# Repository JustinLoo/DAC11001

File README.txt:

the ape4ad5791 is the finished design by GH, the DAC11001 is my design that im basing off of the ape4ad5791. the goal is to make ape4ad5791 but with a different main IC being the DAC11001. both layout connections should be the same. same io and interface.

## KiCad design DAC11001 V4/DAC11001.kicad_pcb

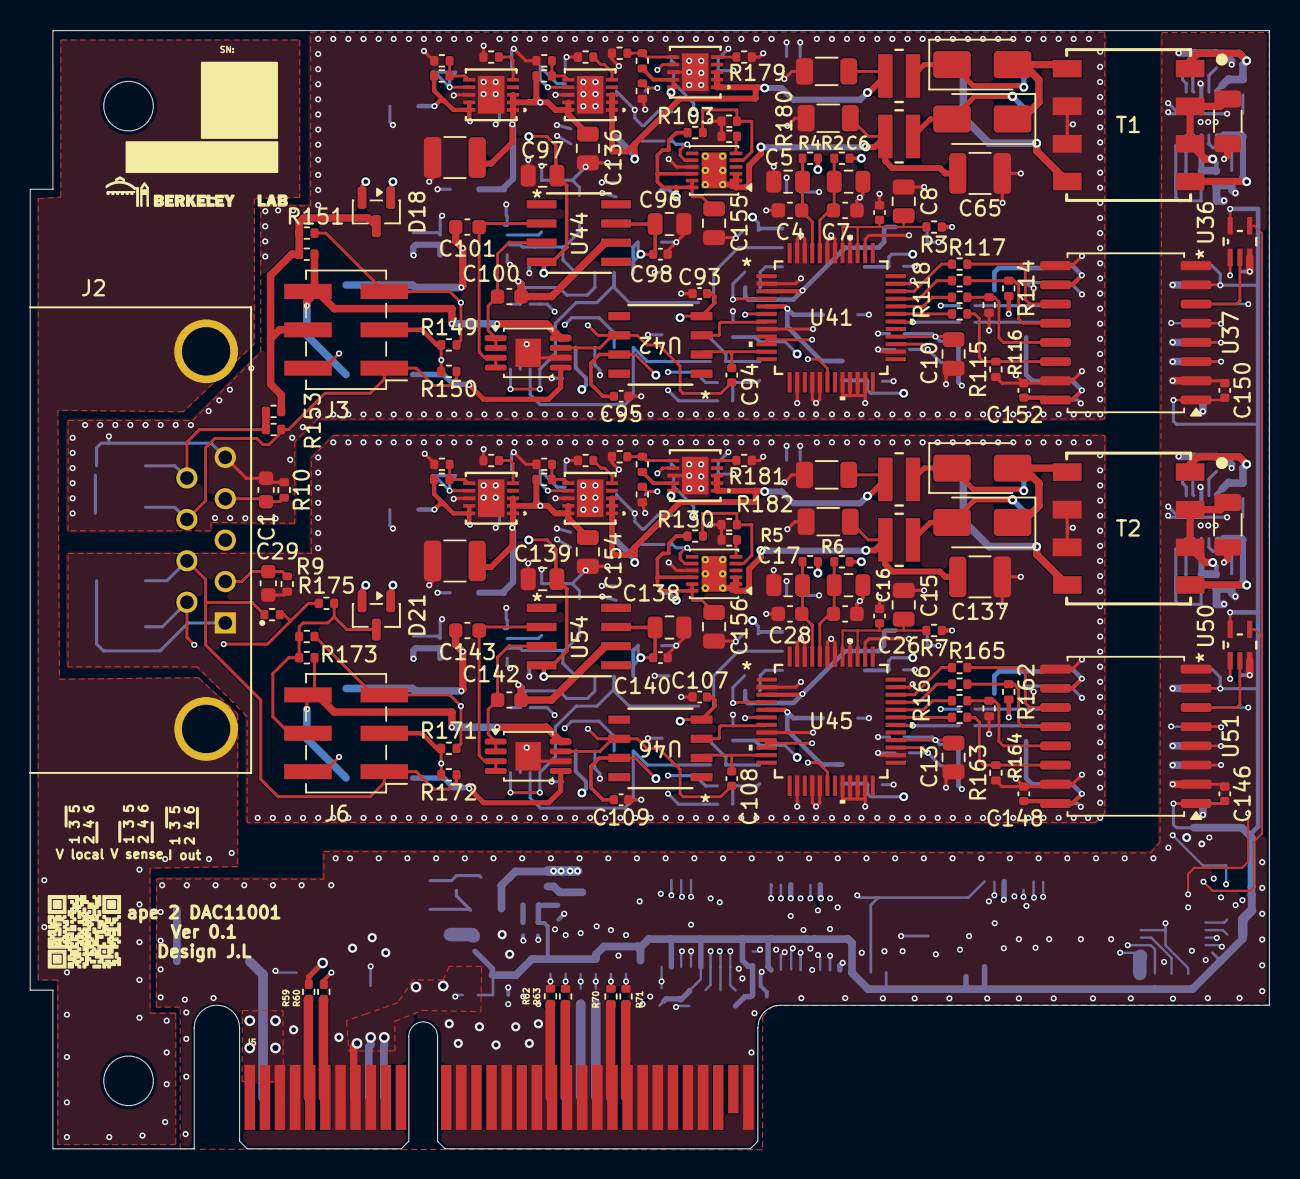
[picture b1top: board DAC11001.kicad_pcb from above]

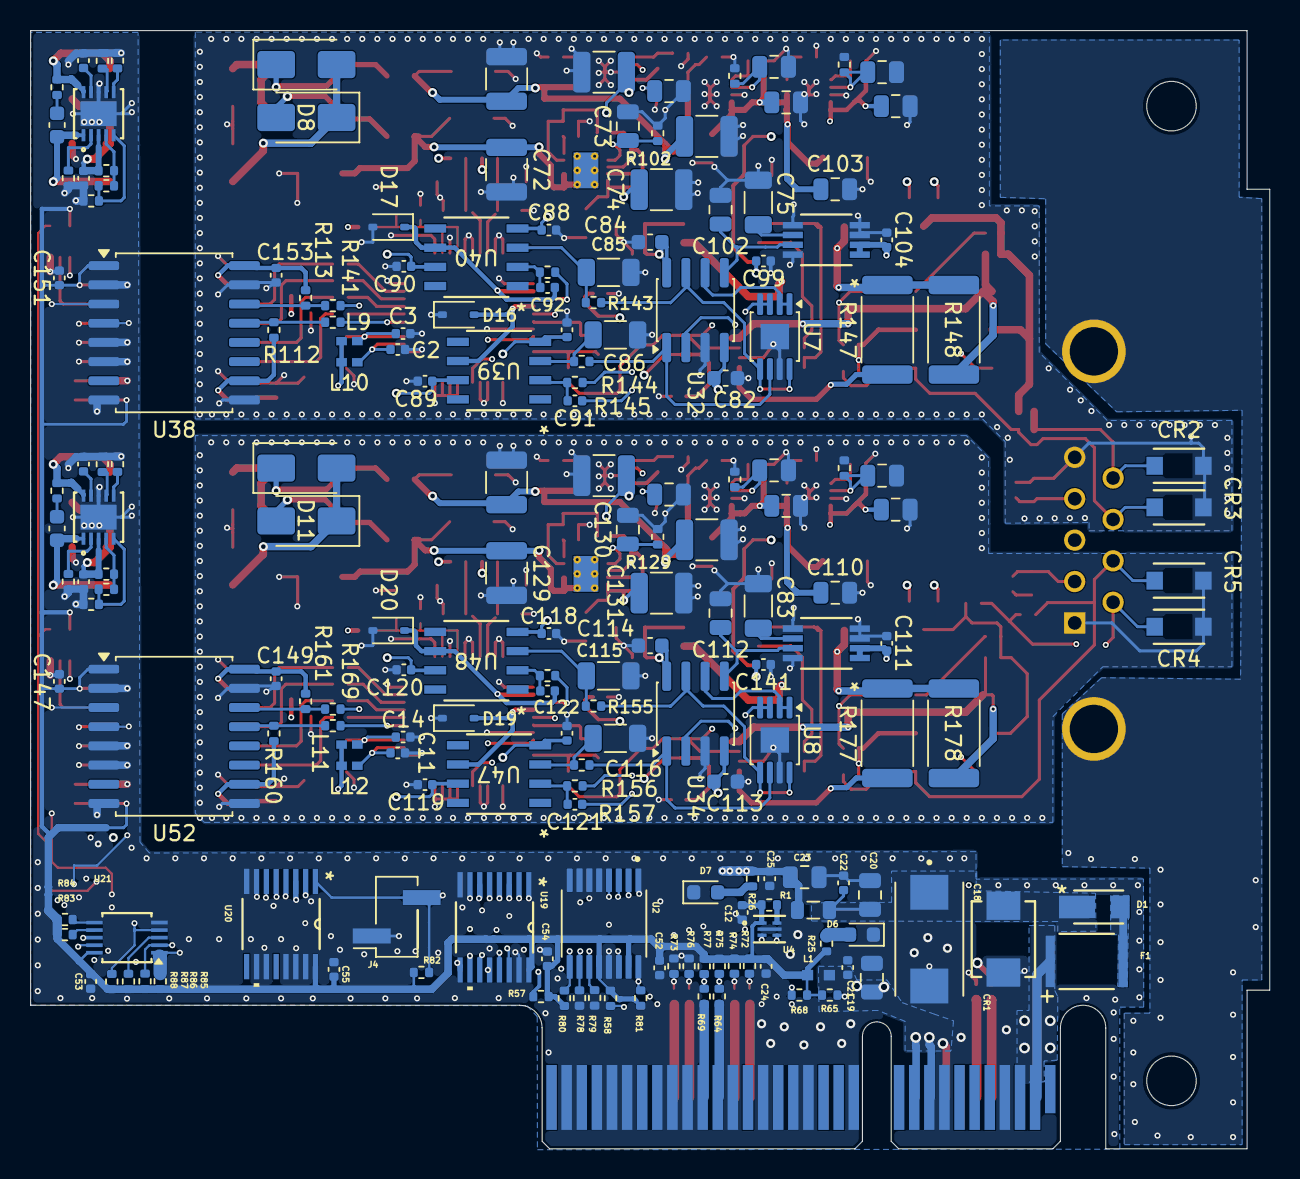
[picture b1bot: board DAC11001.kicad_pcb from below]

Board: 6 copper layers, 82.0 x 74.0 mm, 340 parts (188 on the bottom side), 200 nets.

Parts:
C1, C29: 1nF 50V C0G; C_0603_1608Metric
C2, C3, C11, C14, C87, C88, C89, C90, C93, C95, C107, C109, C117, C118, C119, C120, C146, C147, C148, C149, C150, C151, C152, C153: 0.1uF 50V X7R; C_0402_1005Metric
C4, C7, C26, C28: 1uF 50V X7R; C_0603_1608Metric
C5, C6, C16, C17, C96, C97, C103, C110, C138, C139: 10uF 35V X5R; C_0805_2012Metric
C8, C10, C13, C15, C19: 10uF 16V X5R; C_0805_2012Metric
C9, C27: 1uF 16V X5R; C_0402_1005Metric
C12, C21, C22, C24, C25, C52, C53, C54, C55, C98, C99, C104, C105, C111, C133, C140, C141: 100nF 50V X7R; C_0402_1005Metric
C18: 100uF 25V; CAPPM7343X310N
C20, C23, C67, C70, C73, C77, C80, C124, C127, C130: 4.7uF 50V X5R; C_0805_2012Metric
C62, C134: 180pF C0G 100V; C_0603_1608Metric
C63, C135: 0.01uF 50V X7R; C_0402_1005Metric
C65, C66, C68, C69, C71, C72, C123, C125, C126, C128, C129, C137: 10uF 50V X7R; C_1210_3225Metric
C74, C131: 22uF 35V X7R; C_1210_3225Metric
C75, C83, C85, C86, C115, C116: 1uF C0G 25V; C_1206_3216Metric
C76, C78, C79, C81, C102, C112, C136, C154, C155, C156: 10uF 25V X7R; C_0805_2012Metric
C82, C84, C113, C114: 0.1uF 50V X7R; C_0603_1608Metric
C91, C92, C94, C108, C121, C122: 100pF 50V C0G; C_0402_1005Metric
C100, C142: 10pF 50V C0G; C_0603_1608Metric
C101, C143: 22pF 50V C0G; C_0603_1608Metric
C106, C132: 10uF 25V X7R; C_1206_3216Metric
CR1: SMBJ15A; DO-214AASMB_J-BEND_LTF
CR2, CR3, CR4, CR5: SMF13CA; SOD-123F_LTF
D1: DFLS130-7; DFLS130-7_DIO
D4, D5, D8, D9, D10, D11, D12, D13: CMSH1-200HE; D_SMA
D6: LTST-C193KRKT-5A; LED_0603_1608Metric
D7: LTST-C193TBKT-5A; LED_0603_1608Metric
D16, D17, D19, D20: RB751V40; D_SOD-323
D18, D21: BAV199; SOT-23
F1: Polyfuse; FUS_MINISMDC110F_TYCO_TYC
J2: LD09S13A4GV00LF; AMPHENOL_LD09S13A4GV00LF
J3, J6: Conn_02x03_Odd_Even; PinHeader_2x03_P2.54mm_Vertical_SMD
J4: Conn_01x02; PinHeader_1x02_P2.54mm_Vertical_SMD_Pin1Right
J5: Bus_PCI_Express_x4; BUS_PCIexpress_x4_noedge
L1: WE-CBF_0603; WE-CBF_0603_W2.2
L2: BLM21PG221SN1D; L_0805_2012Metric
L5, L6, L7, L8: 39uH; IND_XFL3012_COC
L9, L10, L11, L12: BLM15AG601SN1D; IND_BLM15_0402_MUR
R1: 4k75; R_0402_1005Metric
R2, R3, R6, R7: 10; R_0402_1005Metric
R4, R5: 1; R_0402_1005Metric
R9, R10, R57, R58, R65, R68, R72, R73, R74, R75, R76, R77, R78, R79, R80, R81, R82, R83, R84, R85, R86, R87, R88, R96, R100, R108, R112, R113, R114, R115, R116, R119, R123, R127, R160, R161, R162, R163, R164: 10k; R_0402_1005Metric
R25: 1.2k; R_0402_1005Metric
R26: 18k; R_0402_1005Metric
R56, R132: 715k; R_0402_1005Metric
R59, R60, R143, R144, R154, R155, R156, R176: 100; R_0402_1005Metric
R61, R133: 36.5k; R_0402_1005Metric
R62, R63, R64, R69, R70, R71, R153, R175: 50; R_0402_1005Metric
R66, R134: 66.5k; R_0402_1005Metric
R67, R135: 49.9k; R_0402_1005Metric
R89, R136: 14.7k; R_0402_1005Metric
R90, R137: 12.1k; R_0402_1005Metric
R91, R138: 39k; R_0402_1005Metric
R93, R124: 1.24k; R_0402_1005Metric
R94, R125: 121k 0.1%; R_0402_1005Metric
R95, R126: 348k; R_0402_1005Metric
R97, R120: 750; R_0402_1005Metric
R98, R121: 154k 0.1%; R_0402_1005Metric
R99, R122: 442k; R_0402_1005Metric
R101, R128: 22.6k; R_0402_1005Metric
R102, R129: 165k 0.1%; R_0402_1005Metric
R103, R130: 220k; R_0402_1005Metric
R104, R131: 4.99k; R_0402_1005Metric
R105, R109: 2.49k; R_0402_1005Metric
R106, R110: 49.9k 0.1%; R_0402_1005Metric
R107, R111: 140k; R_0402_1005Metric
R117, R118, R139, R140, R141, R142, R165, R166, R167, R168, R169, R170: 33; R_0402_1005Metric
R145, R146, R157, R158: 22; R_0402_1005Metric
R147, R148, R177, R178: 500 0.01%; R_2512_6332Metric
R149, R150, R151, R152, R171, R172, R173, R174: 0; R_0402_1005Metric
R179, R180, R181, R182: 1.8k; R_1206_3216Metric
T1, T2: WE-PPTI_EP7; WE-PPTI_EP7_L9.14W9.78H10.54
U2: SC18IS606PWJ; SOP65P640X110-16N
U3, U6: LT3999EDD-PBF; WFDFN10_3X3_ADI
U4: M24128-BFMH6TG; UFDFPN5_1P7X1P4_STM
U7, U8: LT5400AIMS8E-1-PBF; MSOP-8-1EP_3x3mm_P0.65mm_EP1.68x1.88mm
U19, U20: SN74LVC157APWR; PW16
U21: PCA9537; TSSOP-10_3x3mm_P0.5mm
U23, U24, U27, U30, U31, U35: LT3042IDD-TRPBF; DFN-10_DD_LIT
U28, U49: LT3094xDD; DFN-12-1EP_3x3mm_P0.45mm_EP1.65x2.38mm_ThermalVias
U29, U33: LTC6655LNBHMS8-5-PBF; 05-08-1660_ADI
U32, U34: OPA2189xD; SOIC-8_3.9x4.9mm_P1.27mm
U36, U50: SN74LVC1G125DCKR; DCK5
U37, U51: ADuM1401xRW; SOIC-16W_7.5x10.3mm_P1.27mm
U38, U52: ADuM1400xRW; SOIC-16W_7.5x10.3mm_P1.27mm
U39, U40, U42, U46, U47, U48: OPA828ID; D8_TEX
U41, U45: DAC11001BPFBT; PQFP48_DAC11001_TEX
U43, U53: LT5400ACMS8E-1-PBF-func; MSOP-8-1EP_3x3mm_P0.65mm_EP1.68x1.88mm
U44, U54: ADA4523-1BRZ; R-8_ADI

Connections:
/DC3V3: C19.1, C21.1, J5.A9 (+3.3V), J5.A10 (+3.3V), J5.B8 (+3.3V), L1.1
/DC12V: F1.1, J5.A2 (+12V), J5.A3 (+12V), J5.B1 (+12V), J5.B2 (+12V), J5.B3 (+12V)
/HSI1N: J5.A22 (PERn1), R69.1
/HSI1P: J5.A21 (PERp1), R64.1
/HSO1N: J5.B20 (PETn1), R63.1
/HSO1P: J5.B19 (PETp1), R62.1
/HSO2N: J5.B24 (PETn2), R71.1
/HSO2P: J5.B23 (PETp2), R70.1
/I2C_SCL: R59.1, R65.2, U2.2 (SCL), U4.4 (SCL), U21.8 (SCL)
/I2C_SDA: R60.1, R68.2, U2.1 (SDA), U4.3 (SDA), U21.9 (SDA)
/OUT1: CR2.1, J2.09, R153.1, R154.2
/OUT2: CR4.1, J2.06, R175.1, R176.2
/SENSE1: CR3.1, J2.08, J3.1, R150.1, R154.1
/SENSE2: CR5.1, J2.07, J6.1, R172.1, R176.1
/SGND1: C1.2, J2.04, R10.2
/SGND2: C29.2, J2.02, R9.2
/SHIELD: J2.SH1 (SHIELD), J2.SH2 (SHIELD)
/ctrlpins/A0B1: J4.2, R82.2, U19.1 (A/*B), U20.1 (A/*B)
/ctrlpins/VDD: C12.1, C24.1, C52.1, C53.1, C54.1, C55.1, C146.1, C147.1, C150.1, C151.1, L1.2, R1.1, R25.1, R57.1, R58.1, R65.1, R68.1, R72.1, R74.1, R75.1, R77.2, R80.2, R81.2, R82.1, R83.2, R84.2, R85.2, R86.2, R87.2, R88.2, U2.12 (VDD), U2.15 (VREFP), U4.1 (VCC), U19.16 (VCC), U20.16 (VCC), U21.10 (VDD), U36.5 (VCC), U37.1 (VDD1), U37.7 (VE1), U38.1 (VDD1), U50.5 (VCC), U51.1 (VDD1), U51.7 (VE1), U52.1 (VDD1)
/ctrlpins/exCSB1: R62.2, R72.2, U19.11 (3A)
/ctrlpins/exCSB2: R63.2, R74.2, U19.14 (4A)
/ctrlpins/exLDAC: R64.2, R75.2, U20.2 (1A), U20.5 (2A)
/ctrlpins/exMISO: R69.2, R77.1, U2.14 (MISO), U36.4 (Y), U50.4 (Y)
/ctrlpins/exMOSI: R70.2, R76.1, U19.5 (2A)
/ctrlpins/exSCLK: R71.2, R73.1, U19.2 (1A)
/ctrlpins/i2cCSB1: R80.1, U2.9 (~SS0/GPIO0), U19.10 (3B)
/ctrlpins/i2cCSB2: R81.1, U2.16 (~SS1/GPIO1), U19.13 (4B)
/ctrlpins/i2cLDAC1: R85.1, U20.3 (1B), U21.1 (IO0)
/ctrlpins/i2cLDAC2: R86.1, U20.6 (2B), U21.2 (IO1)
/ctrlpins/i2cMOSI1: R78.2, U2.10 (MOSI), U19.6 (2B)
/ctrlpins/i2cSCLK1: R79.2, U2.11 (SPICLK), U19.3 (1B)
/eeprom/WC: R1.2, U4.5 (WC)
/pcie4x/I2CCLK: J5.B5 (SMCLK), R59.2
/pcie4x/I2CSDA: J5.B6 (SMDAT), R60.2
/powerin/DC12Vout: C23.1, C25.1, C105.1, C106.1, C132.1, C133.1, L2.2, R26.1, R56.1, R132.1, T1.2, T1.3, T2.2, T2.3, U3.3 (VIN), U6.3 (VIN)
/top_1/DAC11001/DVDD: C78.1, C152.1, C153.1, L9.1, L10.1, R3.1, R107.1, R112.2, R113.2, R114.2, U30.9 (OUTS), U30.10 (OUT), U37.10 (VE2), U37.16 (VDD2), U38.10 (VE2), U38.16 (VDD2)
/top_1/DAC11001/RCM: C94.1, U41.11 (RCM), U42.2 ('-IN)
/top_1/DAC11001/RFB: J3.3, R149.1, R150.2, U41.9 (RFB), U41.10 (ROFS)
/top_1/DAC11001/V_DAC_OUT: U41.7 (OUT), U42.3 ('+IN)
/top_1/DAC11001/V_REFNF: C91.1, D16.2 (A), U39.6 (OUT), U41.5 (REFNF)
/top_1/DAC11001/V_REFNS: R145.2, U41.6 (REFNS)
/top_1/DAC11001/V_REFPF: C92.1, D17.1 (K), U40.6 (OUT), U41.3 (REFPF)
/top_1/DAC11001/V_REFPS: R146.2, U41.4 (REFPS)
/top_1/I_CLR: R140.2, U41.30 (CLR)
/top_1/I_LDAC: R141.2, U41.18 (LDAC)
/top_1/I_SCLK: R142.2, U41.31 (SCLK)
/top_1/I_SDIN: R139.2, U41.32 (SDIN)
/top_1/I_SDO: R117.2, U41.34 (SDO)
/top_1/I_SYNC: R118.2, U41.33 (SYNC)
/top_1/LT3042/V_P_+18.5V: C66.1, C69.1, L5.1, R179.1, U23.1 (IN), U23.2 (IN), U23.3 (EN/UV), U27.1 (IN), U27.2 (IN), U27.3 (EN/UV)
/top_1/LT3042v2/V_P_+12V: C68.1, C76.1, C103.1, C104.1, C136.1, R95.1, U23.9 (OUTS), U23.10 (OUT), U29.1 (*SHDN), U29.2 (VIN), U30.1 (IN), U30.2 (IN), U30.3 (EN/UV)
/top_1/LT3094/V_P_-18.5V: C65.1, C72.1, L6.1, R180.1, U28.1 (IN), U28.2 (IN), U28.3 (EN/UV), U28.13 (IN)
/top_1/LTC6655/V_LN_5: C102.1, U29.7 (VOUT_F), U32.5 (+)
/top_1/OPA2189/r1in: U7.1 (R1), U7.2 (R2), U32.6 (-)
/top_1/OPA2189/r1out: R143.2, U7.5 (R4), U7.8 (R1), U32.7
/top_1/OPA2189/r3in: U7.3 (R3), U7.4 (R4), U32.2 (-)
/top_1/OPA2189/r3out: R144.2, U7.6 (R3), U32.1
/top_1/OUT STAGE/howland/Iout: J3.6, R148.1, R152.1, U43.8 (R1)
/top_1/OUT STAGE/howland/Vin: C94.2, J3.2, J3.5, R149.2, R151.2, U42.6 (OUT), U43.7 (R2)
/top_1/V_P_C_+15.4V: C71.1, C84.1, C89.1, C90.1, C95.1, C96.1, C98.1, D18.2, R4.1, R99.1, U27.9 (OUTS), U27.10 (OUT), U32.8 (V+), U39.7 (V+), U40.7 (V+), U42.7 (V+), U44.7 (V+)
/top_1/V_P_C_-16.5V: C74.1, C82.1, C87.1, C88.1, C93.1, C97.2, C99.2, C155.1, D18.1, R2.1, R103.1, U28.10 (OUTS), U28.11 (OUT), U28.12 (OUT), U32.4 (V-), U39.4 (V-), U40.4 (V-), U42.4 (V-), U44.4 (V-)
/top_1/adum/VIA1: U19.4 (1Y), U37.3 (VIA), U51.3 (VIA)
/top_1/adum/VIA2: U20.4 (1Y), U38.3 (VIA)
/top_1/adum/VIB1: U19.7 (2Y), U37.4 (VIB), U51.4 (VIB)
/top_1/adum/VIB2: R88.1, U21.4 (IO3), U38.4 (VIB), U52.4 (VIB)
/top_1/adum/VIC1: U19.9 (3Y), U36.1 (*OE), U37.5 (VIC)
/top_1/adum/VID1: R117.1, U37.11 (VID)
/top_1/adum/VOA1: R115.2, R142.1, U37.14 (VOA)
/top_1/adum/VOA2: R113.1, R141.1, U38.14 (VOA)
/top_1/adum/VOB1: R116.2, R139.1, U37.13 (VOB)
/top_1/adum/VOB2: R112.1, R140.1, U38.13 (VOB)
/top_1/adum/VOC1: R114.1, R118.1, U37.12 (VOC)
/top_1/adum/VOD1: U36.2 (A), U37.6 (VOD)
/top_2/DAC11001/DVDD: C81.1, C148.1, C149.1, L11.1, L12.1, R7.1, R111.1, R160.2, R161.2, R162.2, U31.9 (OUTS), U31.10 (OUT), U51.10 (VE2), U51.16 (VDD2), U52.10 (VE2), U52.16 (VDD2)
/top_2/DAC11001/RCM: C108.1, U45.11 (RCM), U46.2 ('-IN)
/top_2/DAC11001/RFB: J6.3, R171.1, R172.2, U45.9 (RFB), U45.10 (ROFS)
/top_2/DAC11001/V_DAC_OUT: U45.7 (OUT), U46.3 ('+IN)
/top_2/DAC11001/V_REFNF: C121.1, D19.2 (A), U45.5 (REFNF), U47.6 (OUT)
/top_2/DAC11001/V_REFNS: R157.2, U45.6 (REFNS)
/top_2/DAC11001/V_REFPF: C122.1, D20.1 (K), U45.3 (REFPF), U48.6 (OUT)
/top_2/DAC11001/V_REFPS: R158.2, U45.4 (REFPS)
/top_2/I_CLR: R168.2, U45.30 (CLR)
/top_2/I_LDAC: R169.2, U45.18 (LDAC)
/top_2/I_SCLK: R170.2, U45.31 (SCLK)
/top_2/I_SDIN: R167.2, U45.32 (SDIN)
/top_2/I_SDO: R165.2, U45.34 (SDO)
/top_2/I_SYNC: R166.2, U45.33 (SYNC)
/top_2/LT3042/V_P_+18.5V: C123.1, C126.1, L7.1, R181.1, U24.1 (IN), U24.2 (IN), U24.3 (EN/UV), U35.1 (IN), U35.2 (IN), U35.3 (EN/UV)
/top_2/LT3042v2/V_P_+12V: C79.1, C110.1, C111.1, C128.1, C154.1, R126.1, U24.9 (OUTS), U24.10 (OUT), U31.1 (IN), U31.2 (IN), U31.3 (EN/UV), U33.1 (*SHDN), U33.2 (VIN)
/top_2/LT3094/V_P_-18.5V: C129.1, C137.1, L8.1, R182.1, U49.1 (IN), U49.2 (IN), U49.3 (EN/UV), U49.13 (IN)
/top_2/LTC6655/V_LN_5: C112.1, U33.7 (VOUT_F), U34.5 (+)
/top_2/OPA2189/r1in: U8.1 (R1), U8.2 (R2), U34.6 (-)
/top_2/OPA2189/r1out: R155.2, U8.5 (R4), U8.8 (R1), U34.7
/top_2/OPA2189/r3in: U8.3 (R3), U8.4 (R4), U34.2 (-)
/top_2/OPA2189/r3out: R156.2, U8.6 (R3), U34.1
/top_2/OUT STAGE/howland/Iout: J6.6, R174.1, R178.1, U53.8 (R1)
/top_2/OUT STAGE/howland/Vin: C108.2, J6.2, J6.5, R171.2, R173.2, U46.6 (OUT), U53.7 (R2)
/top_2/V_P_C_+15.4V: C109.1, C114.1, C119.1, C120.1, C125.1, C138.1, C140.1, D21.2, R5.1, R122.1, U34.8 (V+), U35.9 (OUTS), U35.10 (OUT), U46.7 (V+), U47.7 (V+), U48.7 (V+), U54.7 (V+)
/top_2/V_P_C_-16.5V: C107.1, C113.1, C117.1, C118.1, C131.1, C139.2, C141.2, C156.1, D21.1, R6.1, R130.1, U34.4 (V-), U46.4 (V-), U47.4 (V-), U48.4 (V-), U49.10 (OUTS), U49.11 (OUT), U49.12 (OUT), U54.4 (V-)
/top_2/adum/VIA2: U20.7 (2Y), U52.3 (VIA)
/top_2/adum/VIC1: U19.12 (4Y), U50.1 (*OE), U51.5 (VIC)
/top_2/adum/VID1: R165.1, U51.11 (VID)
/top_2/adum/VOA1: R163.2, R170.1, U51.14 (VOA)
/top_2/adum/VOA2: R161.1, R169.1, U52.14 (VOA)
/top_2/adum/VOB1: R164.2, R167.1, U51.13 (VOB)
/top_2/adum/VOB2: R160.1, R168.1, U52.13 (VOB)
/top_2/adum/VOC1: R162.1, R166.1, U51.12 (VOC)
/top_2/adum/VOD1: U50.2 (A), U51.6 (VOD)
GND: C12.2, C18.2, C19.2, C20.2, C21.2, C22.2, C23.2, C24.2, C25.2, C52.2, C53.2, C54.2, C55.2, C63.2, C105.2, C106.2, C132.2, C133.2, C135.2, C146.2, C147.2, C150.2, C151.2, CR1.2, D6.1 (K), D7.1 (K), J4.1, J5.A4 (GND), J5.A8 (JTAG5), J5.A12 (GND), J5.A15 (GND), J5.A18 (GND), J5.A20 (GND), J5.A23 (GND), J5.A24 (GND), J5.A27 (GND), J5.A28 (GND), J5.A31 (GND), J5.B4 (GND), J5.B7 (GND), J5.B9 (JTAG1), J5.B13 (GND), J5.B16 (GND), J5.B18 (GND), J5.B21 (GND), J5.B22 (GND), J5.B25 (GND), J5.B26 (GND), J5.B29 (GND), J5.B32 (GND), R66.2, R67.2, R73.2, R76.2, R78.1, R79.1, R89.2, R90.2, R134.2, R135.2, R136.2, R137.2, U2.5 (A2), U2.6 (A1), U2.7 (A0), U2.13 (VSS), U3.8 (SYNC), U3.11 (GND), U4.2 (VSS), U6.8 (SYNC), U6.11 (GND), U19.8 (GND), U19.15 (*G), U20.8 (GND), U20.10 (3B), U20.11 (3A), U20.13 (4B), U20.14 (4A), U20.15 (*G), U21.5 (VSS), U36.3 (GND), U37.2 (GND1), U37.8 (GND1), U38.2 (GND1), U38.5 (VIC), U38.6 (VID), U38.8 (GND1), U50.3 (GND), U51.2 (GND1), U51.8 (GND1), U52.2 (GND1), U52.5 (VIC), U52.6 (VID), U52.8 (GND1)
GNDA1: C1.1, C2.2, C3.2, C4.2, C5.2, C6.2, C7.2, C8.2, C9.2, C10.2, C65.2, C66.2, C67.2, C68.2, C69.2, C70.2, C71.2, C72.2, C73.2, C74.2, C75.2, C76.2, C77.2, C78.2, C82.2, C84.2, C85.2, C86.2, C87.2, C88.2, C89.2, C90.2, C93.2, C95.2, C96.2, C97.1, C98.2, C99.1, C102.2, C103.2, C104.2, C136.2, C152.2, C153.2, C155.2, CR2.2, CR3.2, D16.1 (K), D17.2 (A), J2.05, R10.1, R93.2, R94.2, R96.2, R97.2, R98.2, R100.2, R101.2, R102.2, R104.2, R105.2, R106.2, R108.2, R115.1, R116.1, R179.2, R180.2, T1.6, T1.7, U7.7 (R2), U7.9 (EP), U23.8 (GND), U23.11 (GND), U27.8 (GND), U27.11 (GND), U28.9 (GND), U29.3 (GND), U29.4 (GND), U29.5 (GND), U29.8 (GND), U30.8 (GND), U30.11 (GND), U32.3 (+), U37.9 (GND2), U37.15 (GND2), U38.9 (GND2), U38.15 (GND2), U41.2 (AGND), U41.8 (AGND-OUT), U41.14 (AGND-TNH), U41.16 (DGND), U41.17 (DGND), U41.20 (DGND), U41.21 (DGND), U41.22 (DGND), U41.23 (DGND), U41.26 (DGND), U41.35 (AGND), U41.38 (AGND), U41.40 (AGND), U41.42 (AGND), U41.43 (AGND), U41.46 (AGND), U41.47 (AGND), U43.6 (R3), U43.9 (EPAD)
GNDA2: C11.2, C13.2, C14.2, C15.2, C16.2, C17.2, C26.2, C27.2, C28.2, C29.1, C79.2, C80.2, C81.2, C83.2, C107.2, C109.2, C110.2, C111.2, C112.2, C113.2, C114.2, C115.2, C116.2, C117.2, C118.2, C119.2, C120.2, C123.2, C124.2, C125.2, C126.2, C127.2, C128.2, C129.2, C130.2, C131.2, C137.2, C138.2, C139.1, C140.2, C141.1, C148.2, C149.2, C154.2, C156.2, CR4.2, CR5.2, D19.1 (K), D20.2 (A), J2.01, R9.1, R109.2, R110.2, R119.2, R120.2, R121.2, R123.2, R124.2, R125.2, R127.2, R128.2, R129.2, R131.2, R163.1, R164.1, R181.2, R182.2, T2.6, T2.7, U8.7 (R2), U8.9 (EP), U24.8 (GND), U24.11 (GND), U31.8 (GND), U31.11 (GND), U33.3 (GND), U33.4 (GND), U33.5 (GND), U33.8 (GND), U34.3 (+), U35.8 (GND), U35.11 (GND), U45.2 (AGND), U45.8 (AGND-OUT), U45.14 (AGND-TNH), U45.16 (DGND), U45.17 (DGND), U45.20 (DGND), U45.21 (DGND), U45.22 (DGND), U45.23 (DGND), U45.26 (DGND), U45.35 (AGND), U45.38 (AGND), U45.40 (AGND), U45.42 (AGND), U45.43 (AGND), U45.46 (AGND), U45.47 (AGND), U49.9 (GND), U51.9 (GND2), U51.15 (GND2), U52.9 (GND2), U52.15 (GND2), U53.6 (R3), U53.9 (EPAD)
unnamed: C8.1, C9.1, R3.2, U41.39 (AVDD), U41.41 (AVDD)
unnamed: C15.1, C27.1, R7.2, U45.39 (AVDD), U45.41 (AVDD)
unnamed: C18.1, C20.1, C22.1, CR1.1, D1.C, L2.1
unnamed: C62.2, R91.1
unnamed: C134.2, R138.1
unnamed: D1.A, F1.2
unnamed: D4.2 (A), D8.1 (K), T1.5
unnamed: D4.1 (K), D9.1 (K), L5.2
unnamed: D6.2 (A), R25.2
unnamed: D7.2 (A), R26.2
unnamed: D8.2 (A), D10.2 (A), L6.2
unnamed: D9.2 (A), D10.1 (K), T1.8
unnamed: D11.2 (A), D13.2 (A), L8.2
unnamed: D5.2 (A), D11.1 (K), T2.5
unnamed: D12.2 (A), D13.1 (K), T2.8
unnamed: D5.1 (K), D12.1 (K), L7.2
unnamed: D18.3, J3.4, R151.1, R152.2, R153.2
unnamed: D21.3, J6.4, R173.1, R174.2, R175.2
unnamed: R147.1, U43.5 (R4)
unnamed: R177.1, U53.5 (R4)
unnamed: R58.2, U2.3 (~INT)
unnamed: R57.2, U2.4 (~RESET)
unnamed: C63.1, U3.9 (ILIM/SS)
unnamed: R61.2, R66.1, U3.5 (OVLO/DC)
unnamed: R67.1, U3.2 (RBIAS)
unnamed: R89.1, U3.6 (RDC)
unnamed: R90.1, U3.7 (RT)
unnamed: C62.1, T1.4, U3.1 (SWA)
unnamed: R91.2, T1.1, U3.10 (SWB)
unnamed: R56.2, R61.1, U3.4 (UVLO)
unnamed: C135.1, U6.9 (ILIM/SS)
unnamed: R133.2, R134.1, U6.5 (OVLO/DC)
unnamed: R135.1, U6.2 (RBIAS)
unnamed: R136.1, U6.6 (RDC)
unnamed: R137.1, U6.7 (RT)
unnamed: C134.1, T2.4, U6.1 (SWA)
unnamed: R138.2, T2.1, U6.10 (SWB)
unnamed: R132.2, R133.1, U6.4 (UVLO)
unnamed: R87.1, U21.3 (IO2)
unnamed: R83.1, U21.7 (~INT)
unnamed: R84.1, U21.6 (~RESET)
unnamed: R93.1, U23.5 (ILIM)
unnamed: R95.2, R96.1, U23.6 (PGFB)
unnamed: C67.1, R94.1, U23.7 (SET)
unnamed: R124.1, U24.5 (ILIM)
unnamed: R126.2, R127.1, U24.6 (PGFB)
unnamed: C127.1, R125.1, U24.7 (SET)
unnamed: R97.1, U27.5 (ILIM)
unnamed: R99.2, R100.1, U27.6 (PGFB)
unnamed: C70.1, R98.1, U27.7 (SET)
unnamed: R101.1, U28.6 (ILIM)
unnamed: R103.2, R104.1, U28.5 (PGFB)
unnamed: C73.1, R102.1, U28.8 (SET)
unnamed: C75.1, U29.6 (NR)
unnamed: R105.1, U30.5 (ILIM)
unnamed: R107.2, R108.1, U30.6 (PGFB)
unnamed: C77.1, R106.1, U30.7 (SET)
unnamed: R109.1, U31.5 (ILIM)
unnamed: R111.2, R119.1, U31.6 (PGFB)
unnamed: C80.1, R110.1, U31.7 (SET)
unnamed: C83.1, U33.6 (NR)
unnamed: R120.1, U35.5 (ILIM)
unnamed: R122.2, R123.1, U35.6 (PGFB)
unnamed: C124.1, R121.1, U35.7 (SET)
unnamed: C86.1, R144.1, U39.3 ('+IN)
unnamed: C91.2, R145.1, U39.2 ('-IN)
unnamed: C85.1, R143.1, U40.3 ('+IN)
unnamed: C92.2, R146.1, U40.2 ('-IN)
unnamed: C2.1, L10.2, U41.27 (DVDD)
unnamed: C3.1, C10.1, L9.2, U41.28 (IOVDD)
unnamed: C4.1, C5.1, R4.2, U41.45 (VCC)
unnamed: C6.1, C7.1, R2.2, U41.44 (VSS)
unnamed: C100.1, U43.1 (R1), U43.2 (R2), U44.3 (+IN)
unnamed: C101.1, U43.3 (R3), U43.4 (R4), U44.2 (-IN)
unnamed: C100.2, C101.2, R147.2, R148.2, U44.6 (OUT)
unnamed: C11.1, L12.2, U45.27 (DVDD)
unnamed: C13.1, C14.1, L11.2, U45.28 (IOVDD)
unnamed: C17.1, C28.1, R5.2, U45.45 (VCC)
unnamed: C16.1, C26.1, R6.2, U45.44 (VSS)
unnamed: C116.1, R156.1, U47.3 ('+IN)
unnamed: C121.2, R157.1, U47.2 ('-IN)
unnamed: C115.1, R155.1, U48.3 ('+IN)
unnamed: C122.2, R158.1, U48.2 ('-IN)
unnamed: R128.1, U49.6 (ILIM)
unnamed: R130.2, R131.1, U49.5 (PGFB)
unnamed: C130.1, R129.1, U49.8 (SET)
unnamed: C142.1, U53.1 (R1), U53.2 (R2), U54.3 (+IN)
unnamed: C143.1, U53.3 (R3), U53.4 (R4), U54.2 (-IN)
unnamed: C142.2, C143.2, R177.2, R178.2, U54.6 (OUT)

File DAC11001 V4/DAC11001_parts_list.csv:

Qty,References,Value,Footprint,Vendor,MPN,Manufacturer,DNP
2,C1 C29,1nF 50V C0G,C_0603_1608Metric,digikey:490-8275-1-ND,,,
24,C2 C3 C11 C14 C87 C88 C89 C90 C93 C95 C107 C109 C117 C118 C119 C120 C146 C147 C148 C149 C150 C151 C152 C153,0.1uF 50V X7R,C_0402_1005Metric,digikey:490-10700-1-ND,,,
4,C4 C7 C26 C28,1uF 50V X7R,C_0603_1608Metric,,,,
10,C5 C6 C16 C17 C96 C97 C103 C110 C138 C139,10uF 35V X5R,C_0805_2012Metric,digikey:490-12646-1-ND,,,
5,C8 C10 C13 C15 C19,10uF 16V X5R,C_0805_2012Metric,digikey:490-18663-1-ND,,,
2,C9 C27,1uF 16V X5R,C_0402_1005Metric,digikey:490-10018-1-ND,,,
17,C12 C21 C22 C24 C25 C52 C53 C54 C55 C98 C99 C104 C105 C111 C133 C140 C141,100nF 50V X7R,C_0402_1005Metric,digikey:490-10700-1-ND,,,
1,C18,100uF 25V,CAPPM7343X310N,digikey:718-2173-1-ND,,,
10,C20 C23 C67 C70 C73 C77 C80 C124 C127 C130,4.7uF 50V X5R,C_0805_2012Metric,digikey:490-10751-1-ND,,,
2,C62 C134,180pF C0G 100V,C_0603_1608Metric,,GRM3195C2A181JA01D,Murata,
2,C63 C135,0.01uF 50V X7R,C_0402_1005Metric,,,,
12,C65 C66 C68 C69 C71 C72 C123 C125 C126 C128 C129 C137,10uF 50V X7R,C_1210_3225Metric,,GRM32ER71H106KA12L,Murata,
2,C74 C131,22uF 35V X7R,C_1210_3225Metric,,GRM32ER7YA226MA12L,Murata,
6,C75 C83 C85 C86 C115 C116,1uF C0G 25V,C_1206_3216Metric,,C3216C0G1E105J160AC,TDK,
10,C76 C79 C136 C154 C155 C156 C78 C81 C102 C112,10uF 25V X7R,C_0805_2012Metric,,"C2012X7R1E106K125AB, CL31B106KAHNNNE, GRM21BR71E106KA73L",TDK,
4,C82 C84 C113 C114,0.1uF 50V X7R,C_0603_1608Metric,,,,
6,C91 C92 C94 C108 C121 C122,100pF 50V C0G,C_0402_1005Metric,,,,
2,C100 C142,10pF 50V C0G,C_0603_1608Metric,digikey:490-6086-1-ND,,,
2,C101 C143,22pF 50V C0G,C_0603_1608Metric,digikey:490-16699-1-ND,,,
2,C106 C132,10uF 25V X7R,C_1206_3216Metric,,GRM32ER71H106KA12L,Murata,
1,CR1,SMBJ15A,DO-214AASMB_J-BEND_LTF,digikey:SMBJ15ALFCT-ND,,,
4,CR2 CR3 CR4 CR5,SMF13CA,SOD-123F_LTF,digikey:SMF13CA,,,
1,D1,DFLS130-7,DFLS130-7_DIO,digikey:DFLS130DICT-ND,,,
8,D4 D5 D8 D9 D10 D11 D12 D13,CMSH1-200HE,D_SMA,,,,
1,D6,LTST-C193KRKT-5A,LED_0603_1608Metric,digikey:160-1830-1-ND,,,
1,D7,LTST-C193TBKT-5A,LED_0603_1608Metric,digikey:160-1827-1-ND,,,
4,D16 D17 D19 D20,RB751V40,D_SOD-323,,RB751V40T1G,onsemi,
2,D18 D21,BAV199,SOT-23,digikey:5399-BAV199CT-ND,,,
1,F1,Polyfuse,FUS_MINISMDC110F_TYCO_TYC,digikey:MINISMDC110F-2CT-ND,,,
1,J2,LD09S13A4GV00LF,AMPHENOL_LD09S13A4GV00LF,digikey:609-5188-ND,,,
2,J3 J6,Conn_02x03_Odd_Even,PinHeader_2x03_P2.54mm_Vertical_SMD,digikey:WM17457-ND,,,
1,J4,Conn_01x02,PinHeader_1x02_P2.54mm_Vertical_SMD_Pin1Right,digikey:SAM8979-ND,,,
1,J5,Bus_PCI_Express_x4,BUS_PCIexpress_x4_noedge,,,,
1,L1,WE-CBF_0603,WE-CBF_0603_W2.2,digikey:732-1582-1-ND,,,
1,L2,BLM21PG221SN1D,L_0805_2012Metric,digikey:490-1054-1-ND,BLM21PG221SN1D,Murata,
4,L5 L6 L7 L8,39uH,IND_XFL3012_COC,,XFL3012-393MEC,Coilcraft,
4,L9 L10 L11 L12,BLM15AG601SN1D,IND_BLM15_0402_MUR,,BLM15AG601SN1D,Murata,
1,R1,4k75,R_0402_1005Metric,digikey:YAG1271CT-ND,,,DNP
4,R2 R3 R6 R7,10,R_0402_1005Metric,digikey:YAG3438CT-ND,,,
2,R4 R5,1,R_0402_1005Metric,,,,
37,R9 R10 R57 R58 R72 R73 R74 R75 R76 R77 R78 R79 R80 R81 R82 R83 R84 R85 R86 R87 R88 R96 R100 R108 R112 R113 R114 R115 R116 R119 R123 R127 R160 R161 R162 R163 R164,10k,R_0402_1005Metric,digikey:311-10KJRCT-ND,,,
1,R25,1.2k,R_0402_1005Metric,digikey:311-1.2KJRCT-ND,,,
1,R26,18k,R_0402_1005Metric,digikey:311-18.0KLRCT-ND,,,
2,R56 R132,715k,R_0402_1005Metric,,,,
8,R59 R60 R143 R144 R154 R155 R156 R176,100,R_0402_1005Metric,digikey:YAG3435CT-ND,,,
2,R61 R133,36.5k,R_0402_1005Metric,,,,
8,R62 R63 R64 R69 R70 R71 R153 R175,50,R_0402_1005Metric,digikey:13-RT0402BRE0750RLCT-ND,,,
2,R65 R68,10k,R_0402_1005Metric,digikey:311-10KJRCT-ND,,,DNP
2,R66 R134,66.5k,R_0402_1005Metric,,,,
2,R67 R135,49.9k,R_0402_1005Metric,digikey:311-49.9KLRCT-ND,,,
2,R89 R136,14.7k,R_0402_1005Metric,,,,
2,R90 R137,12.1k,R_0402_1005Metric,,,,
2,R91 R138,39k,R_0402_1005Metric,,,,
2,R93 R124,1.24k,R_0402_1005Metric,,,,
2,R94 R125,121k 0.1%,R_0402_1005Metric,,RT0402BRD07121KL,Yageo,
2,R95 R126,348k,R_0402_1005Metric,,,,
2,R97 R120,750,R_0402_1005Metric,digikey:311-750LRCT-ND,,,
2,R98 R121,154k 0.1%,R_0402_1005Metric,,RT0402BRD07154KL,Yageo,
2,R99 R122,442k,R_0402_1005Metric,digikey:311-442KLRCT-ND,,,
2,R101 R128,22.6k,R_0402_1005Metric,,,,
2,R102 R129,165k 0.1%,R_0402_1005Metric,,RT0402BRD07165KL,Yageo,
2,R103 R130,220k,R_0402_1005Metric,,,,
2,R104 R131,4.99k,R_0402_1005Metric,,,,
2,R105 R109,2.49k,R_0402_1005Metric,,,,
2,R106 R110,49.9k 0.1%,R_0402_1005Metric,,RT0402BRD0749K9L,Yageo,
2,R107 R111,140k,R_0402_1005Metric,,,,
12,R117 R118 R139 R140 R141 R142 R165 R166 R167 R168 R169 R170,33,R_0402_1005Metric,digikey:13-RT0402BRD0733RLCT-ND,,,
4,R145 R146 R157 R158,22,R_0402_1005Metric,,,,
4,R147 R148 R177 R178,500 0.01%,R_2512_6332Metric,digikey:804-Y4027500R000T9R-ND,,,
8,R149 R150 R151 R152 R171 R172 R173 R174,0,R_0402_1005Metric,digikey:311-0.0LBCT-ND,,,DNP
4,R179 R180 R181 R182,1.8k,R_1206_3216Metric,,ERJ-P08F1801V,Panasonic,
2,T1 T2,WE-PPTI_EP7,WE-PPTI_EP7_L9.14W9.78H10.54,,,,
1,U2,SC18IS606PWJ,SOP65P640X110-16N,newark:29AK7128,,,
2,U3 U6,LT3999EDD-PBF,WFDFN10_3X3_ADI,,LT3999EDD#PBF,Analog Devices,
1,U4,M24128-BFMH6TG,UFDFPN5_1P7X1P4_STM,digikey:497-17565-1-ND,,,
2,U7 U8,LT5400AIMS8E-1-PBF,MSOP-8-1EP_3x3mm_P0.65mm_EP1.68x1.88mm,,,,
2,U19 U20,SN74LVC157APWR,PW16,digikey:296-1225-1-ND,,,
1,U21,PCA9537,TSSOP-10_3x3mm_P0.5mm,digikey:568-PCA9537DPZCT-ND,,,
6,U23 U24 U27 U30 U31 U35,LT3042IDD-TRPBF,DFN-10_DD_LIT,digikey:LT3042IDD#TRPBFCT-ND,LT3042IDD#TRPBF,Analog Devices,
2,U28 U49,LT3094xDD,DFN-12-1EP_3x3mm_P0.45mm_EP1.65x2.38mm_ThermalVias,digikey:505-LT3094EDD#TRPBFCT-ND,LT3094EDD#TRPBF,Analog Devices,
2,U29 U33,LTC6655LNBHMS8-5-PBF,05-08-1660_ADI,digikey:505-LTC6655LNBHMS8-5#PBF-ND,LTC6655LNBHMS8-5#PBF,Analog Devices,
2,U32 U34,OPA2189xD,SOIC-8_3.9x4.9mm_P1.27mm,,OPA2189IDR,Texas Instruments,
2,U36 U50,SN74LVC1G125DCKR,DCK5,digikey:296-11604-1-ND,SN74LVC1G125DCKR,Texas Instruments,
2,U37 U51,ADuM1401xRW,SOIC-16W_7.5x10.3mm_P1.27mm,digikey:505-ADUM1401BRWZ-ND,,,
2,U38 U52,ADuM1400xRW,SOIC-16W_7.5x10.3mm_P1.27mm,digikey:ADUM1400CRWZ-RLCT-ND,,,
6,U39 U40 U42 U46 U47 U48,OPA828ID,D8_TEX,digikey:296-53407-ND,OPA828IDR,Texas Instruments,
2,U41 U45,DAC11001BPFBT,PQFP48_DAC11001_TEX,,DAC11001BPFBT,Texas Instruments,
2,U43 U53,LT5400ACMS8E-1-PBF-func,MSOP-8-1EP_3x3mm_P0.65mm_EP1.68x1.88mm,digikey:505-LT5400ACMS8E-1#PBF-ND,,,
2,U44 U54,ADA4523-1BRZ,R-8_ADI,digikey:505-ADA4523-1BRZ-ND,,,
